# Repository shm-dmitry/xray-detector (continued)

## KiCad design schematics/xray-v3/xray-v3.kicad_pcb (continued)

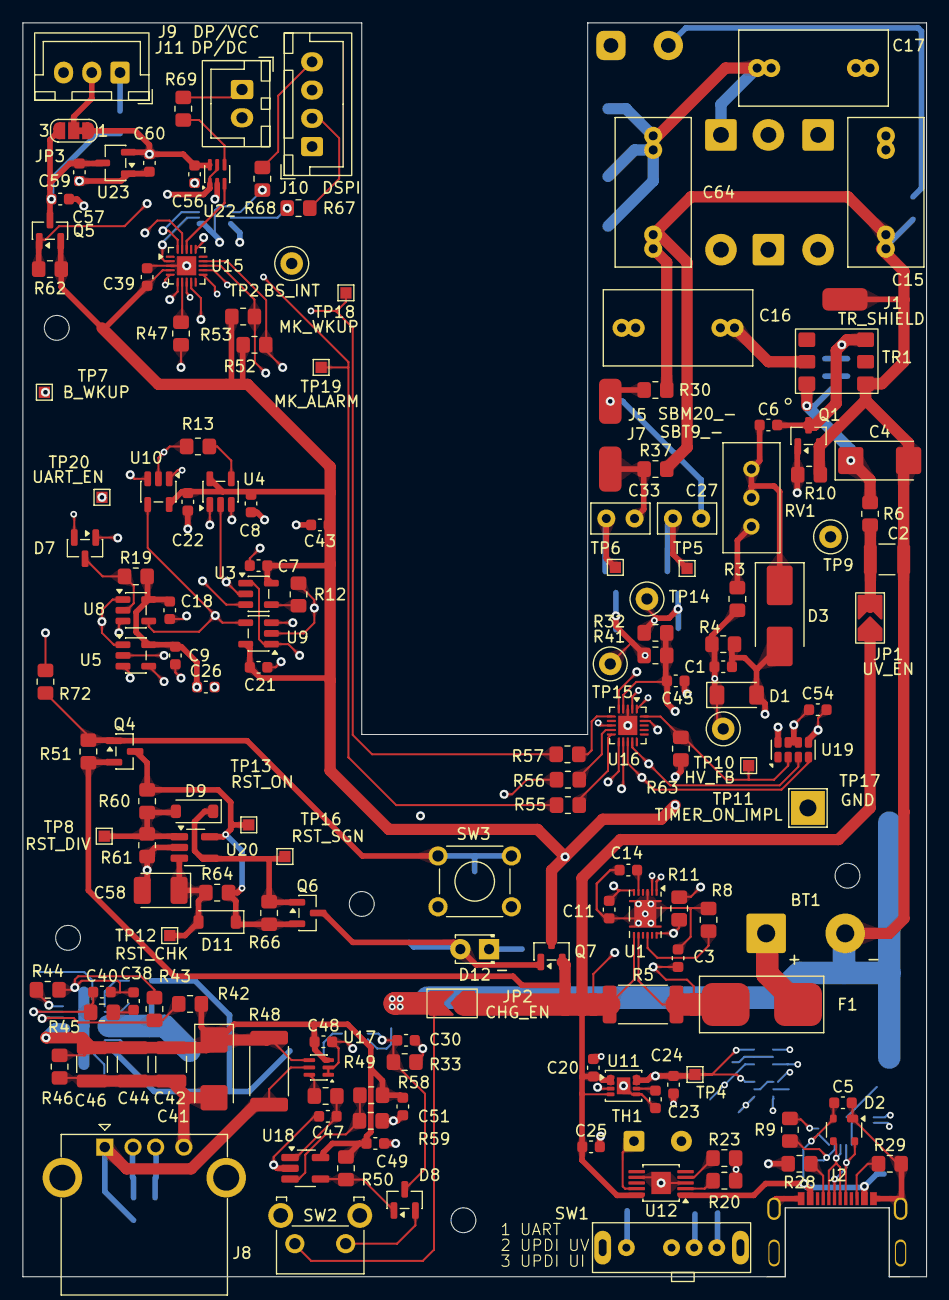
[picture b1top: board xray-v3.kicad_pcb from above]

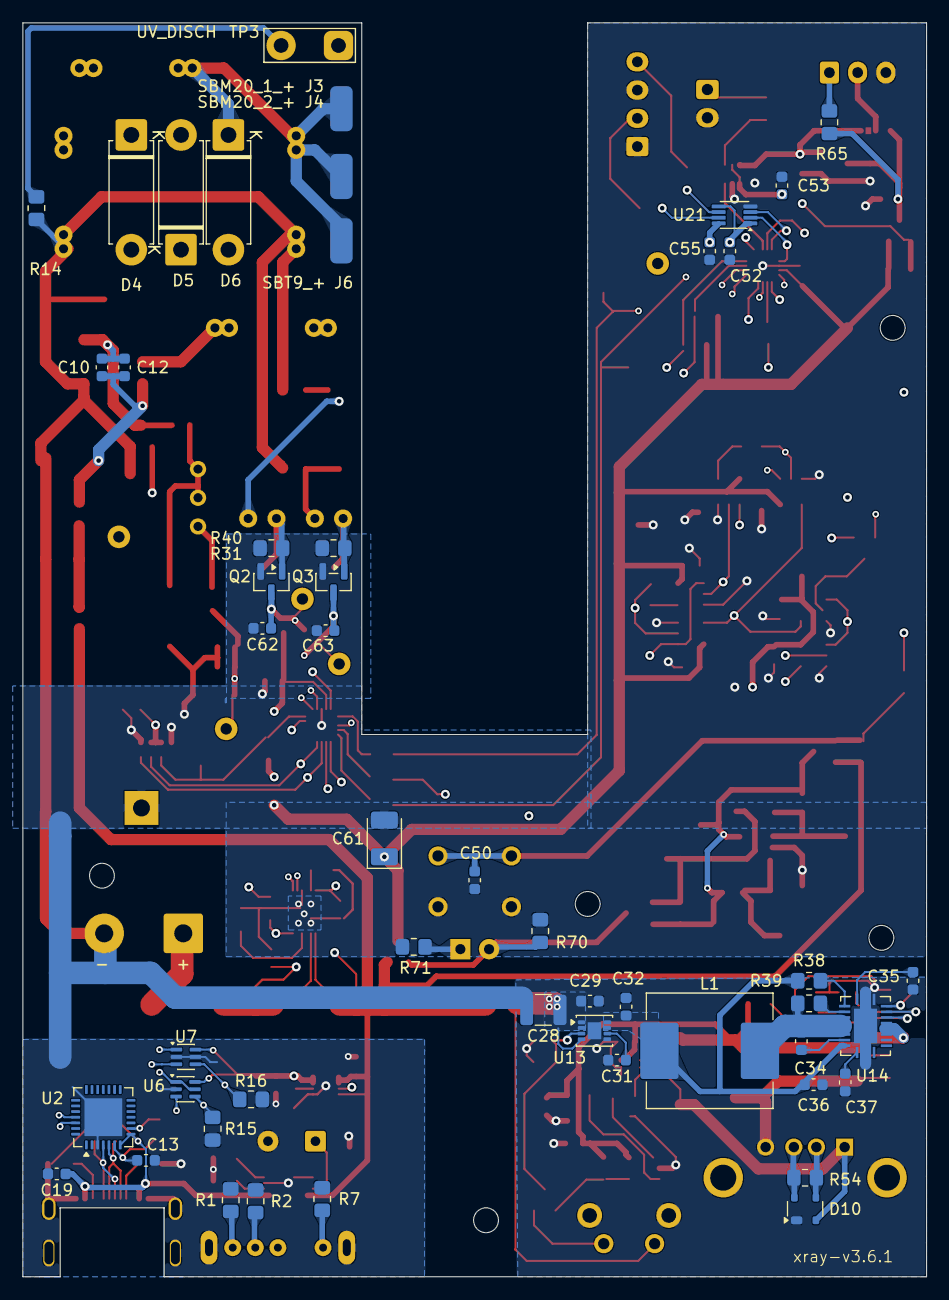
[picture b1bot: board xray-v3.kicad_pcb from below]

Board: 4 copper layers, 80.0 x 111.0 mm, 215 parts (51 on the bottom side), 109 nets.

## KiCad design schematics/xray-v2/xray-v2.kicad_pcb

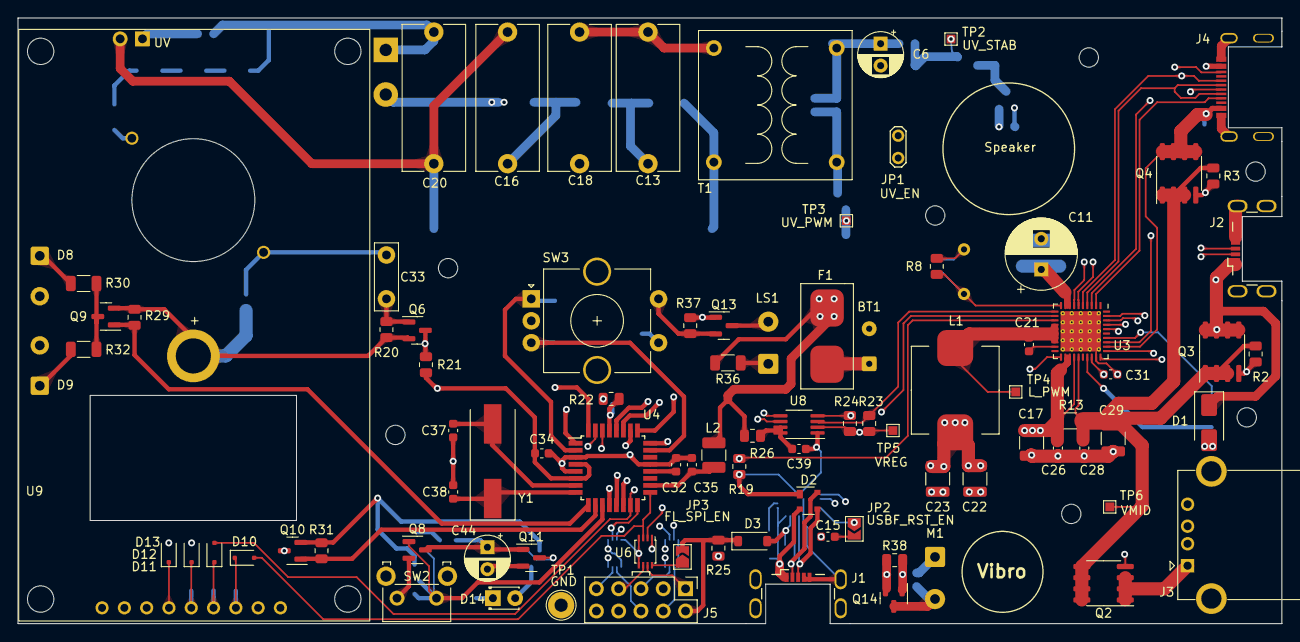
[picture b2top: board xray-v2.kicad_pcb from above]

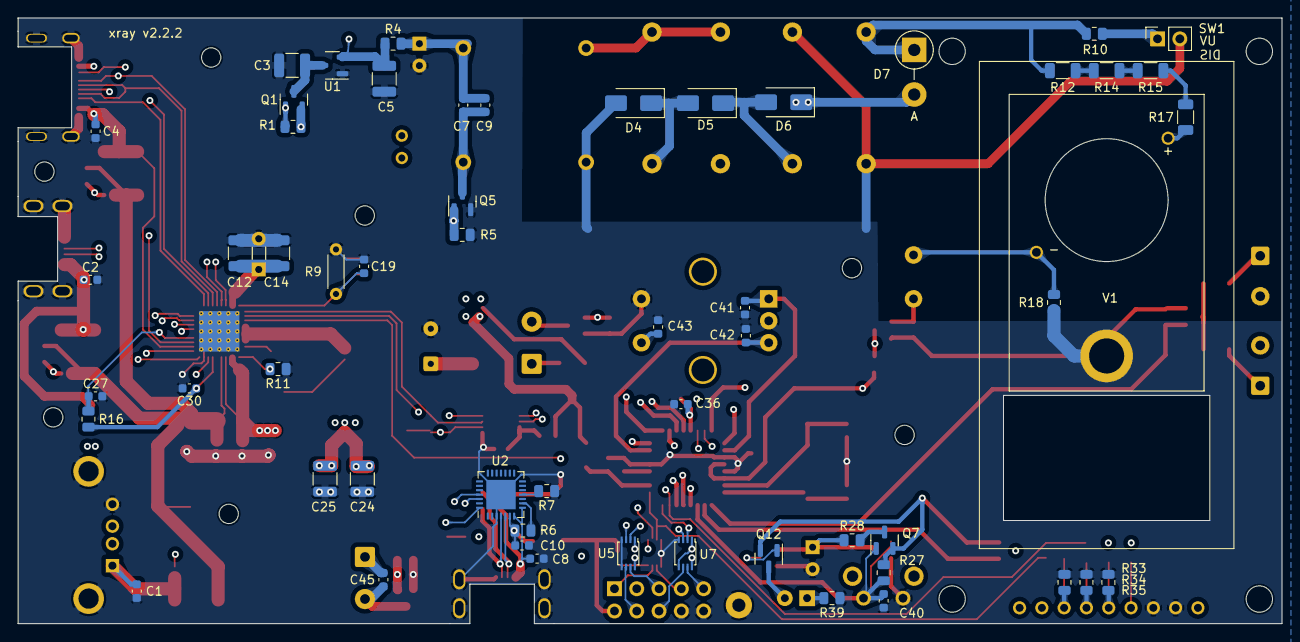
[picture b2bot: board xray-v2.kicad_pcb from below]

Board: 4 copper layers, 144.0 x 69.0 mm, 154 parts (56 on the bottom side), 101 nets.

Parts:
BT1: Li-Ion, 4.2V, 10000 mAh, 1260100; SolderWire-0.15sqmm_1x02_P4mm_D0.5mm_OD1.5mm
C1, C2, C4, C8, C10, C27: 10 uF; C_0603_1608Metric
C3, C5, C12, C14, C17, C22, C23, C24, C25, C29: 22 uF; C_1210_3225Metric
C6, C44: 100 uF; CP_Radial_D5.0mm_P2.50mm
C7: 21 nF *; C_0603_1608Metric
C9: see note [*]; C_0603_1608Metric
C11: 220 uF; CP_Radial_D8.0mm_P3.50mm
C13, C16, C18, C20: К73-17, 0.1 uF, 630V; C_Rect_L16.5mm_W7.0mm_P15.00mm_MKT
C15, C19, C21, C26, C28, C32, C34, C36, C41, C42, C43, C45: 100 nF; C_0603_1608Metric
C30, C31: 2.2 uF; C_0603_1608Metric
C33: CC81, 10 pF, 630V; C_Disc_D7.5mm_W2.5mm_P5.00mm
C35: 470 nF; C_0603_1608Metric
C37, C38: 18 pF; C_0603_1608Metric
C39: 200 pF; C_0603_1608Metric
C40: 2 uF; C_0603_1608Metric
D1: 15MQ030NPBF; D_SMA
D2: SP0503BAHT; SOT-143
D3: MBR0520; D_SOD-123
D4, D5, D6: US1M; D_SMA
D7: US1M; D_5W_P5.08mm_Vertical_AnodeUp
D8, D9: FLASH; SolderWire-0.5sqmm_1x02_P4.6mm_D0.9mm_OD2.1mm
D10, D11, D12, D13: BAV21WS; D_SOD-323F
D14: L-2060YD; LED_D1.8mm_W3.3mm_H2.4mm
F1: 1808, 6A; FuseHolder1808
H1, H2, H3, H4, H5, H6, H7: MountingHole; MountingHole_2.2mm_M2
J1, J2: USB_B_Micro; USB_Micro-B
J3: USB_A
J4: USB_C_Receptacle_USB2.0; USB_C_P16_MIDMOUNT_1.6
J5: USBASP; PinHeader_2x05_P2.54mm_Vertical
JP1: UV_EN; TestPoint_2Pads_Pitch2.54mm_Drill0.8mm
JP2: USBF_RST_EN; SolderJumper-2_P1.3mm_Open_TrianglePad1.0x1.5mm
JP3: FL_SPI_EN; SolderJumper-2_P1.3mm_Open_TrianglePad1.0x1.5mm
L1: 2.2 uH; Ferrocore-HPI1040
L2: 20 uH; L_1210_3225Metric
LS1: Speaker, D13mm; SolderWire-0.5sqmm_1x02_P4.8mm_D0.9mm_OD2.3mm
M1: VibroMotor, 3V, 8x2.7mm; SolderWire-0.5sqmm_1x02_P4.8mm_D0.9mm_OD2.3mm
Q1, Q7, Q10, Q12: IRLML5203; SOT-23
Q2: IRF7832PbF; SOIC-8_3.9x4.9mm_P1.27mm
Q3, Q4: IRF7425PbF; SOIC-8_3.9x4.9mm_P1.27mm
Q5, Q8, Q9, Q11, Q13, Q14: IRLML0030; SOT-23
Q6: BC847; SOT-23
R1, R2, R3, R7, R16, R21, R22, R25, R27: 10K; R_0805_2012Metric
R4: 68; R_0805_2012Metric
R5, R18, R20, R26, R29, R31, R37, R38: 200K; R_0805_2012Metric
R6: 1K; R_0805_2012Metric
R8: 82K; R_0805_2012Metric
R9: NTCM-100K@25-B4250; R_Axial_DIN0204_L3.6mm_D1.6mm_P5.08mm_Horizontal
R10: 510; R_0805_2012Metric
R11: 114K; R_0805_2012Metric
R12, R14, R15, R17: 2M, 200V; R_1206_3216Metric
R13: 0.01; R_1206_3216Metric
R19: 510K; R_0805_2012Metric
R23, R24: 3.3K; R_0805_2012Metric
R28: 400K ****; R_0805_2012Metric
R30, R32: 16; R_1206_3216Metric
R33, R34, R35: 5K; R_0805_2012Metric
R36: 27; R_1206_3216Metric
R39: 620; R_0805_2012Metric
SW1: SW_Push; PinSocket_1x02_P2.54mm_Vertical
SW2: B3F3150; SW_Tactile_SKHH_Angled
SW3: EC11W****; RotaryEncoder_Alps_EC11E-Switch_Vertical_H20mm_CircularMoun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
T1: Transformer_1P_1S; transformator-4-sh4x4
TP1: GND; TestPoint_Loop_D2.54mm_Drill1.5mm_Beaded
TP2: UV_STAB; TestPoint_Pad_1.0x1.0mm
TP3: UV_PWM; TestPoint_Pad_1.0x1.0mm
TP4: L_PWM; TestPoint_Pad_1.0x1.0mm
TP5: VREG; TestPoint_Pad_1.0x1.0mm
TP6: VMID; TestPoint_Pad_1.0x1.0mm
U1: XC6206P282MR; SOT-23-3
U2: CP2102N-Axx-xQFN28; QFN-28-1EP_5x5mm_P0.5mm_EP3.35x3.35mm
U3: IP5328P; QFN-40-1EP_6x6mm_P0.5mm_EP4.6x4.6mm_ThermalVias
U4: ATmega328P-A; TQFP-32_7x7mm_P0.8mm
U5, U6, U7: SN74LVC2T45DCUR; VSSOP-8_2.4x2.1mm_P0.5mm
U8: PCA9306; MSOP-8_3x3mm_P0.65mm
U9: Display_2.2inch_ili9341
V1: SBT11A; SBT11
Y1: HC-49SM, 8MHz; Crystal_SMD_HC49-SD

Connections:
+5V: D3.1 (K), J5.2, JP3.2 (B), R25.2, U5.8 (VCCB), U7.8 (VCCB)
/DISPLAY_VCC: D13.2 (A), Q10.3 (D), U9.1 (VCC), U9.8 (LED)
CP2102_VREG: C10.1, D3.2 (A), R6.2, U2.6 (VDD)
ENCODER_A: C41.1, SW3.A, U4.2 (PD4)
ENCODER_B: C42.1, SW3.B, U4.23 (PC0)
ENCODER_CLICK: C43.1, SW3.S1, U4.12 (PB0)
FLASHLIGHT: Q9.1 (G), R29.2, U4.9 (PD5)
FLUSH_D+: D2.3 (K), J1.3 (D+), U2.4 (D+)
FLUSH_D-: D2.4 (K), J1.2 (D-), U2.5 (D-)
FLUSH_VBUS: C8.1, D1.2 (A), D2.2 (K), J1.1 (VBUS), U2.7 (VREGIN), U2.8 (VBUS)
GND: BT1.2 (-), C1.2, C2.2, C3.2, C4.2, C5.2, C6.2, C8.2, C10.2, C11.2, C12.2, C14.2, C16.1, C17.2, C19.1, C20.1, C22.2, C23.2, C24.2, C25.2, C26.2, C27.2, C28.2, C29.2, C30.2, C31.2, C32.2, C34.2, C35.2, C36.2, C37.2, C38.2, C39.1, C40.1, C41.2, C42.2, C43.2, C44.2, D2.1 (A), D4.2 (A), J1.4 (ID), J1.5 (GND), J1.6 (Shield), J2.4 (ID), J2.5 (GND), J2.6 (Shield), J3.4 (GND), J3.5 (Shield), J4.A1 (GND), J4.A12 (GND), J4.B1 (GND), J4.B12 (GND), J4.S1 (SHIELD), J5.8, J5.10, Q5.2 (S), Q6.2 (E), Q8.2 (S), Q9.2 (S), Q11.2 (S), Q13.2 (S), Q14.2 (S), R5.1, R7.1, R8.2, R9.2, R11.1, R18.1, R19.2, R20.1, R29.1, R33.2, R34.2, R35.2, R37.1, R38.1, R39.1, SW1.2, SW2.2, SW3.C, SW3.S2, T1.3 (SA), TP1.1, U1.1 (GND), U2.3 (GND), U2.29 (GND), U3.29 (AGND), U3.41 (EP), U4.3 (GND), U4.5 (GND), U4.21 (GND), U5.4 (GND), U5.5 (DIR), U6.4 (GND), U6.5 (DIR), U7.4 (GND), U8.1 (GND), U9.2 (GND), U9.3 (CS), V1.3 (S)
MCU_I2C_SCL: U4.28 (PC5), U8.6 (SCL2)
MCU_I2C_SDA: U4.27 (PC4), U8.5 (SDA2)
MISO: U4.16 (PB4), U7.2 (A1)
MOSI: D11.2 (A), U4.15 (PB3), U6.2 (A1)
unnamed: BT1.1 (+), F1.2
unnamed: C13.1, D4.1 (K), D5.2 (A)
unnamed: C16.2, D5.1 (K), D6.2 (A)
unnamed: C18.2, D6.1 (K), D7.2 (A)
unnamed: C20.2, D7.1 (K), R10.2, R12.1
unnamed: D8.1 (K), R30.2
unnamed: D9.1 (K), R32.2
unnamed: D10.1 (K), R35.1, U9.7 (SCK)
unnamed: D11.1 (K), R34.1, U9.6 (MOSI)
unnamed: D12.1 (K), R33.1, U9.5 (DC)
unnamed: D13.1 (K), U9.4 (RESET#)
unnamed: D14.2 (A), Q12.3 (D)
unnamed: D14.1 (K), R39.2
unnamed: J5.1, U6.7 (B1)
unnamed: J5.7, U6.6 (B2)
unnamed: J5.9, U7.7 (B1)
unnamed: JP1.2 (B), Q1.1 (G), R1.1
unnamed: JP2.1 (A), U2.28 (~DTR)
unnamed: C15.1, JP2.2 (B)
unnamed: JP3.1 (A), U6.8 (VCCB)
unnamed: LS1.1, R36.1
unnamed: C45.1, M1.2 (-), Q14.3 (D)
unnamed: C3.1, Q1.3 (D), U1.3 (VI)
unnamed: C7.1, C9.1, Q5.3 (D), T1.2 (AB)
unnamed: C33.2, Q6.1 (B), R20.2
unnamed: Q7.3 (D), R28.2
unnamed: Q9.3 (D), R30.1, R32.1
unnamed: C44.1, Q8.3 (D), Q11.1 (G), R28.1
unnamed: LS1.2, Q13.3 (D)
unnamed: R10.1, SW1.1
unnamed: R12.2, R14.1
unnamed: R14.2, R15.1
unnamed: R15.2, R17.1
unnamed: C6.1, C7.2, C9.2, R4.2, T1.1 (AA)
unnamed: C13.2, C18.1, T1.4 (SB)
unnamed: C5.1, R4.1, TP2.1, U1.2 (VO)
unnamed: R6.1, U2.9 (~RST)
unnamed: R7.2, U2.11 (~SUSPEND)
unnamed: C21.1, U3.19 (BST)
unnamed: C21.2, L1.2, TP4.1, U3.14 (LX_1), U3.15 (LX_2), U3.16 (LX_3), U3.17 (LX_4), U3.18 (LX_5)
unnamed: C19.2, R8.1, R9.1, U3.10 (NTC)
unnamed: R11.2, U3.21 (RSET)
unnamed: C32.1, U4.20 (AREF)
unnamed: C35.1, L2.1, U4.18 (AVCC)
unnamed: C37.1, U4.7 (XTAL1/PB6), Y1.2
unnamed: C38.1, U4.8 (XTAL2/PB7), Y1.1
unnamed: C39.2, R26.2, U8.7 (VREF2), U8.8 (EN)
unnamed: R17.2, V1.1 (A)
unnamed: C33.1, R18.2, V1.2 (C)
RADIATION_VALUE: Q6.3 (C), R21.1, U4.32 (PD2)
RESET: C36.1, Q11.3 (D), Q12.1 (G), R22.1, U4.29 (~RESET/PC6), U5.2 (A1)
RESET_V: C15.2, J5.5, R25.1, U5.7 (B1)
RXD: U4.30 (PD0), U5.3 (A2)
RXD_V: J5.4, U2.26 (TXD), U5.6 (B2)
SCK: D10.2 (A), U4.17 (PB5), U6.3 (A2)
SPEAKER: Q13.1 (G), R37.2, U4.1 (PD3)
TFT_DC: D12.2 (A), U4.26 (PC3)
TFT_ENABLE#: Q10.1 (G), R31.1, U4.10 (PD6)
TXD: U4.31 (PD1), U7.3 (A2)
TXD_V: J5.6, U2.25 (RXD), U7.6 (B2)
USB_I2C_SCL: R23.2, U3.11 (L1), U8.3 (SCL1)
USB_I2C_SDA: R24.2, U3.12 (L2), U8.4 (SDA1)
USB_INT: R19.1, U3.13 (L3), U4.13 (PB1)
USB_IN_CC1: J4.A5 (CC1), U3.2 (CC1)
USB_IN_CC2: J4.B5 (CC2), U3.3 (CC2)
USB_IN_D+: J4.A6 (D+), J4.B6 (D+), U3.5 (DPC)
USB_IN_D-: J4.A7 (D-), J4.B7 (D-), U3.4 (DMC)
USB_IN_VBUS: C4.1, J4.A4 (VBUS), J4.A9 (VBUS), J4.B4 (VBUS), J4.B9 (VBUS), Q4.5 (D), Q4.6 (D), Q4.7 (D), Q4.8 (D), U3.32 (VBUS)
USB_IN_VBUS_G: Q4.4 (G), R3.1, U3.33 (VBUSG)
USB_M_IN_D+: J2.3 (D+), U3.7 (DPB)
USB_M_IN_D-: J2.2 (D-), U3.6 (DMB)
USB_M_IN_VBUS: C2.1, D1.1 (K), J2.1 (VBUS), Q3.5 (D), Q3.6 (D), Q3.7 (D), Q3.8 (D), U3.30 (VIN)
USB_M_IN_VBUS_G: Q3.4 (G), R2.1, U3.31 (VING)
USB_OUT_D+: J3.3 (D+), U3.39 (DPA1)
USB_OUT_D-: J3.2 (D-), U3.38 (DMA1)
USB_OUT_VBUS: C1.1, J3.1 (VBUS), Q2.1 (S), Q2.2 (S), Q2.3 (S), U3.37 (VOUT1)
USB_OUT_VBUS_G: Q2.4 (G), U3.36 (VOUT1G)
USB_OUT_VOUT2: C27.1, R16.2, U3.34 (VOUT2)
USB_VMID: C28.1, C29.1, Q2.5 (D), Q2.6 (D), Q2.7 (D), Q2.8 (D), Q3.1 (S), Q3.2 (S), Q3.3 (S), Q4.1 (S), Q4.2 (S), Q4.3 (S), R2.2, R3.2, R13.1, TP6.1, U3.25 (VSN)
USB_VSYS: C11.1, C12.1, C14.1, C17.1, C26.1, R13.2, U3.8 (VSYS_1), U3.9 (VSYS_2), U3.22 (VSYS_3), U3.23 (VSYS_4), U3.24 (VSP)
UV_ENABLE#: JP1.1 (A), U4.25 (PC2)
UV_PWM: Q5.1 (G), R5.2, TP3.1, U4.14 (PB2)
VCC: C22.1, C23.1, C24.1, C25.1, C31.1, C34.1, C45.2, D8.2 (A), D9.2 (A), F1.1, L1.1, L2.2, M1.1 (+), Q1.2 (S), Q7.2 (S), Q10.2 (S), Q12.2 (S), R1.2, R21.2, R22.2, R26.1, R27.2, R31.2, R36.2, U3.28 (BAT), U4.4 (VCC), U4.6 (VCC), U5.1 (VCCA), U6.1 (VCCA), U7.1 (VCCA), U7.5 (DIR)
VIBRO: Q14.1 (G), R38.2, U4.24 (PC1)
VREG: C30.1, R16.1, R23.1, R24.1, TP5.1, U3.27 (VREG), U8.2 (VREF1)
WAKEUP_BUTTON: C40.2, Q7.1 (G), Q8.1 (G), R27.1, SW2.1, U4.11 (PD7)

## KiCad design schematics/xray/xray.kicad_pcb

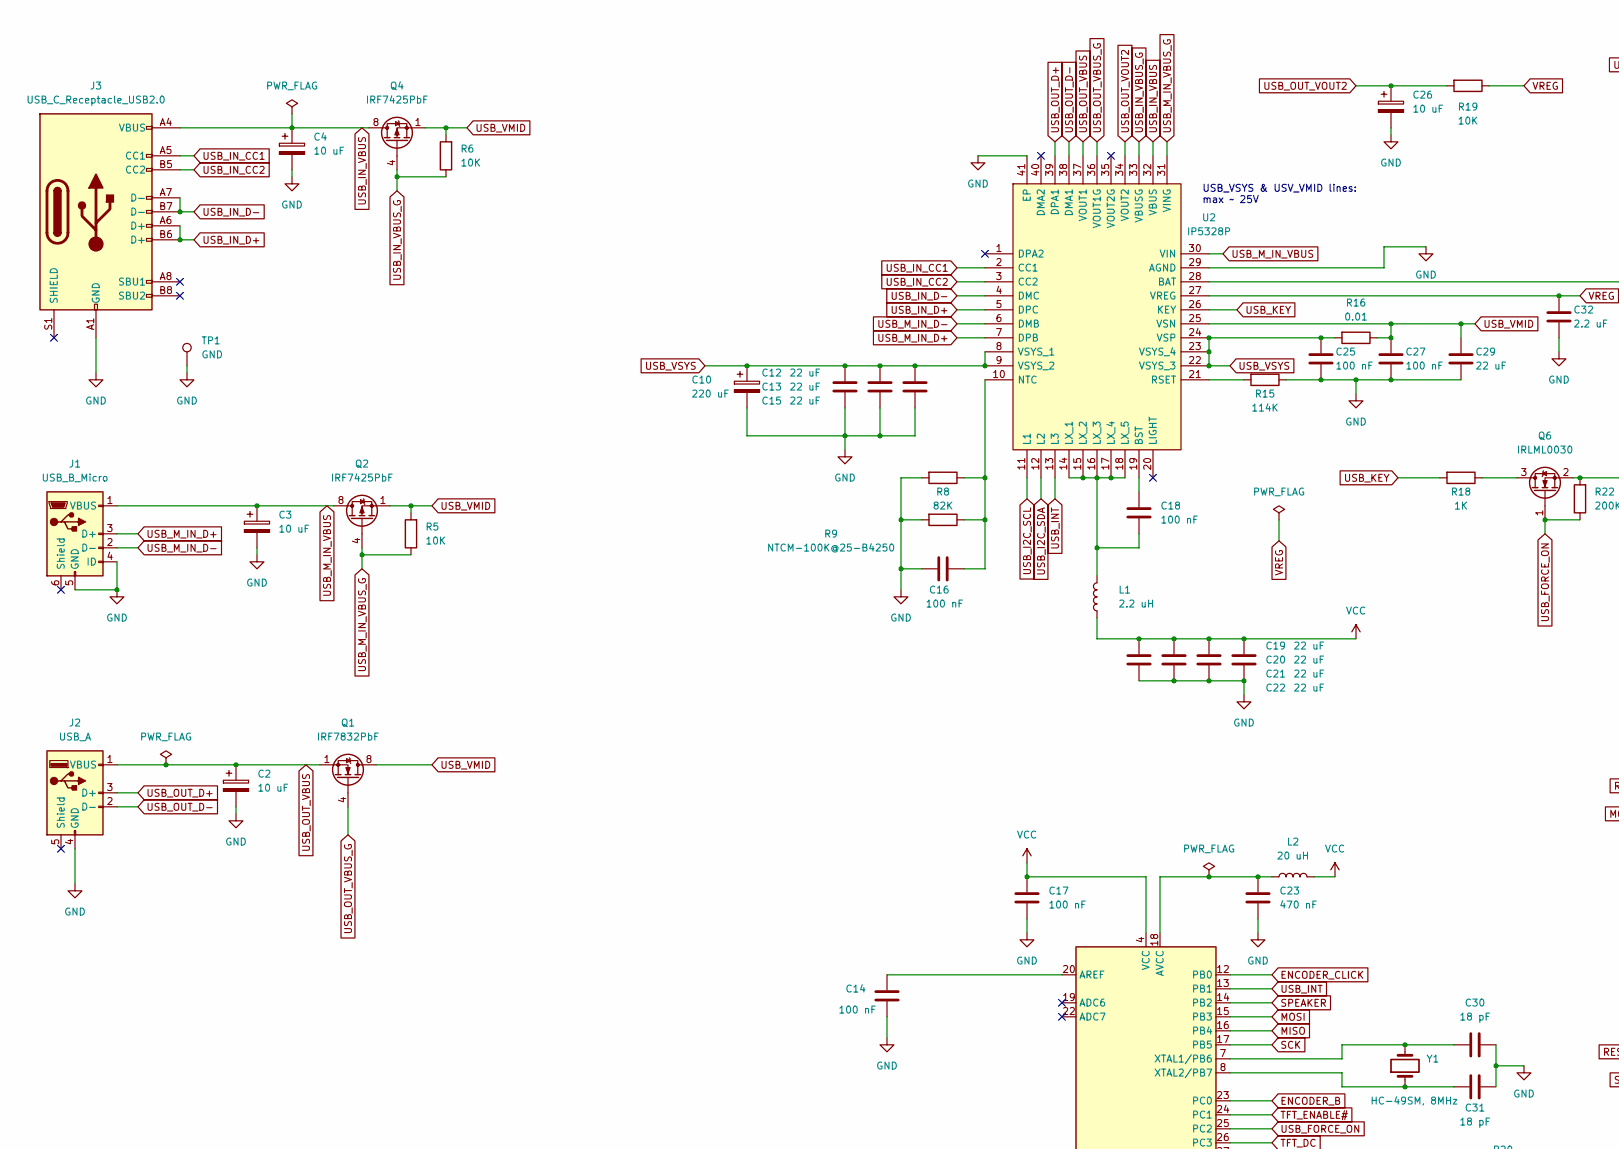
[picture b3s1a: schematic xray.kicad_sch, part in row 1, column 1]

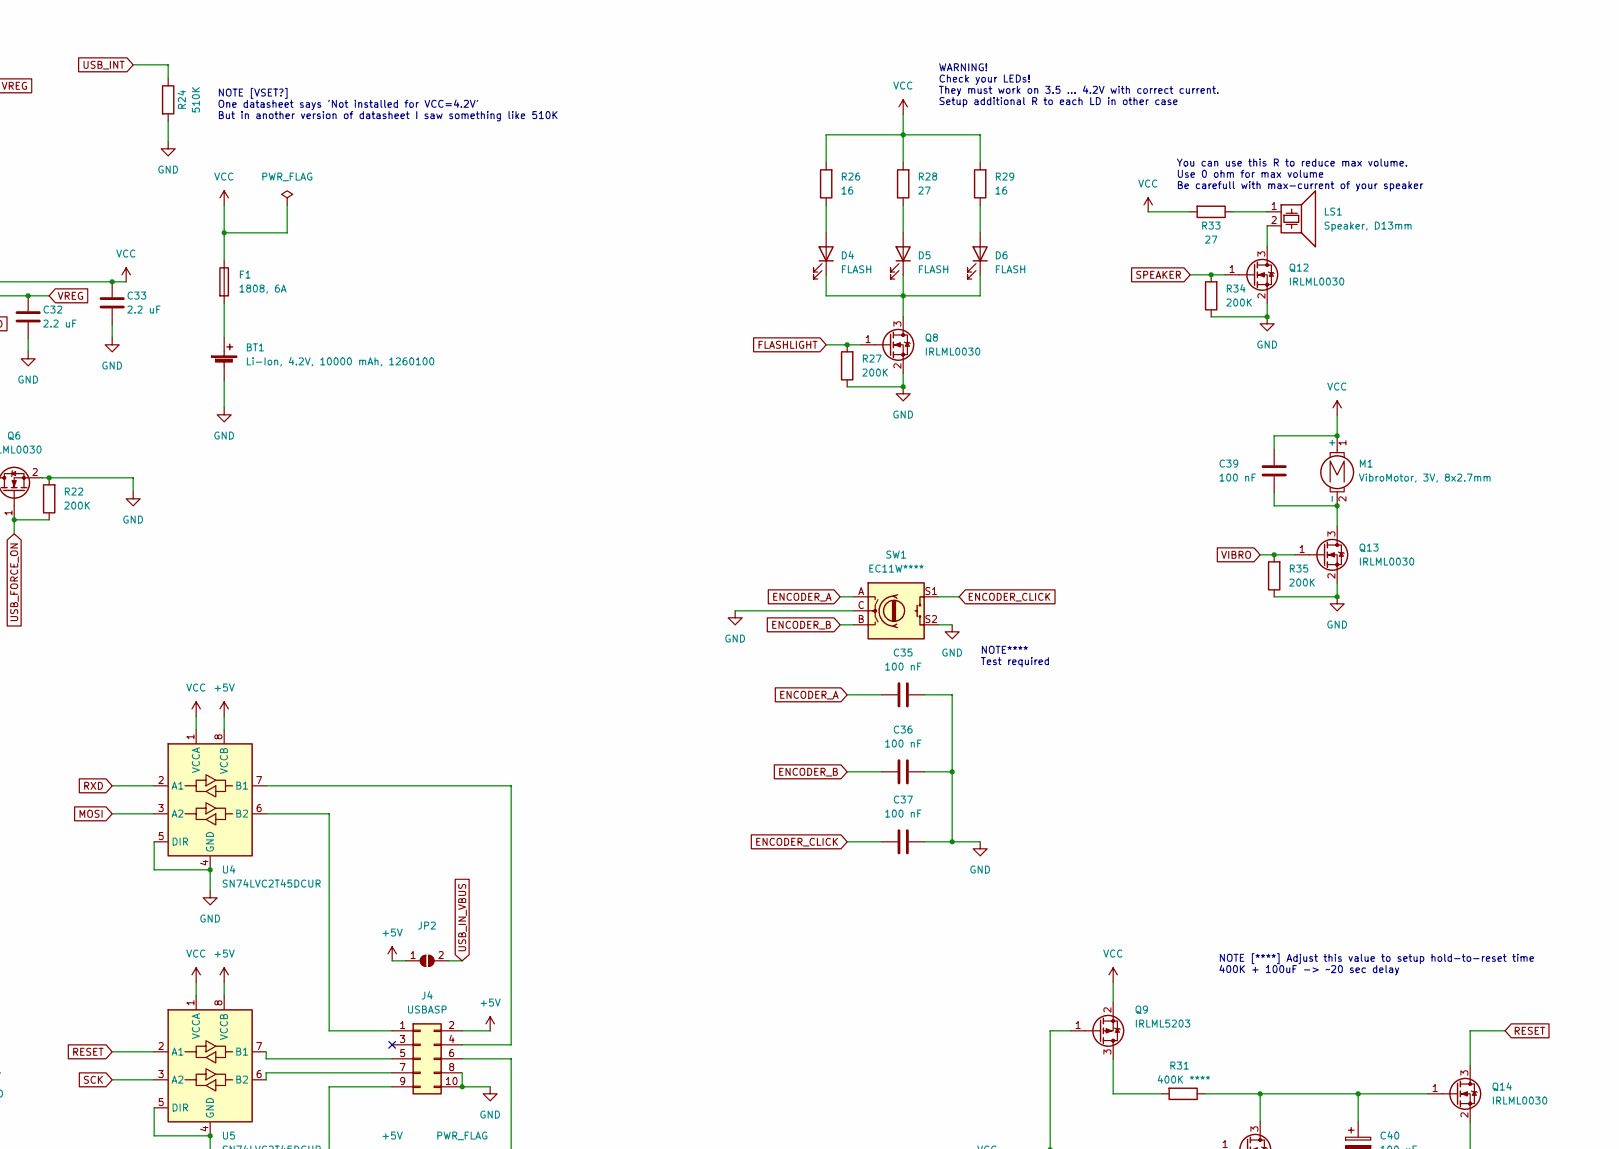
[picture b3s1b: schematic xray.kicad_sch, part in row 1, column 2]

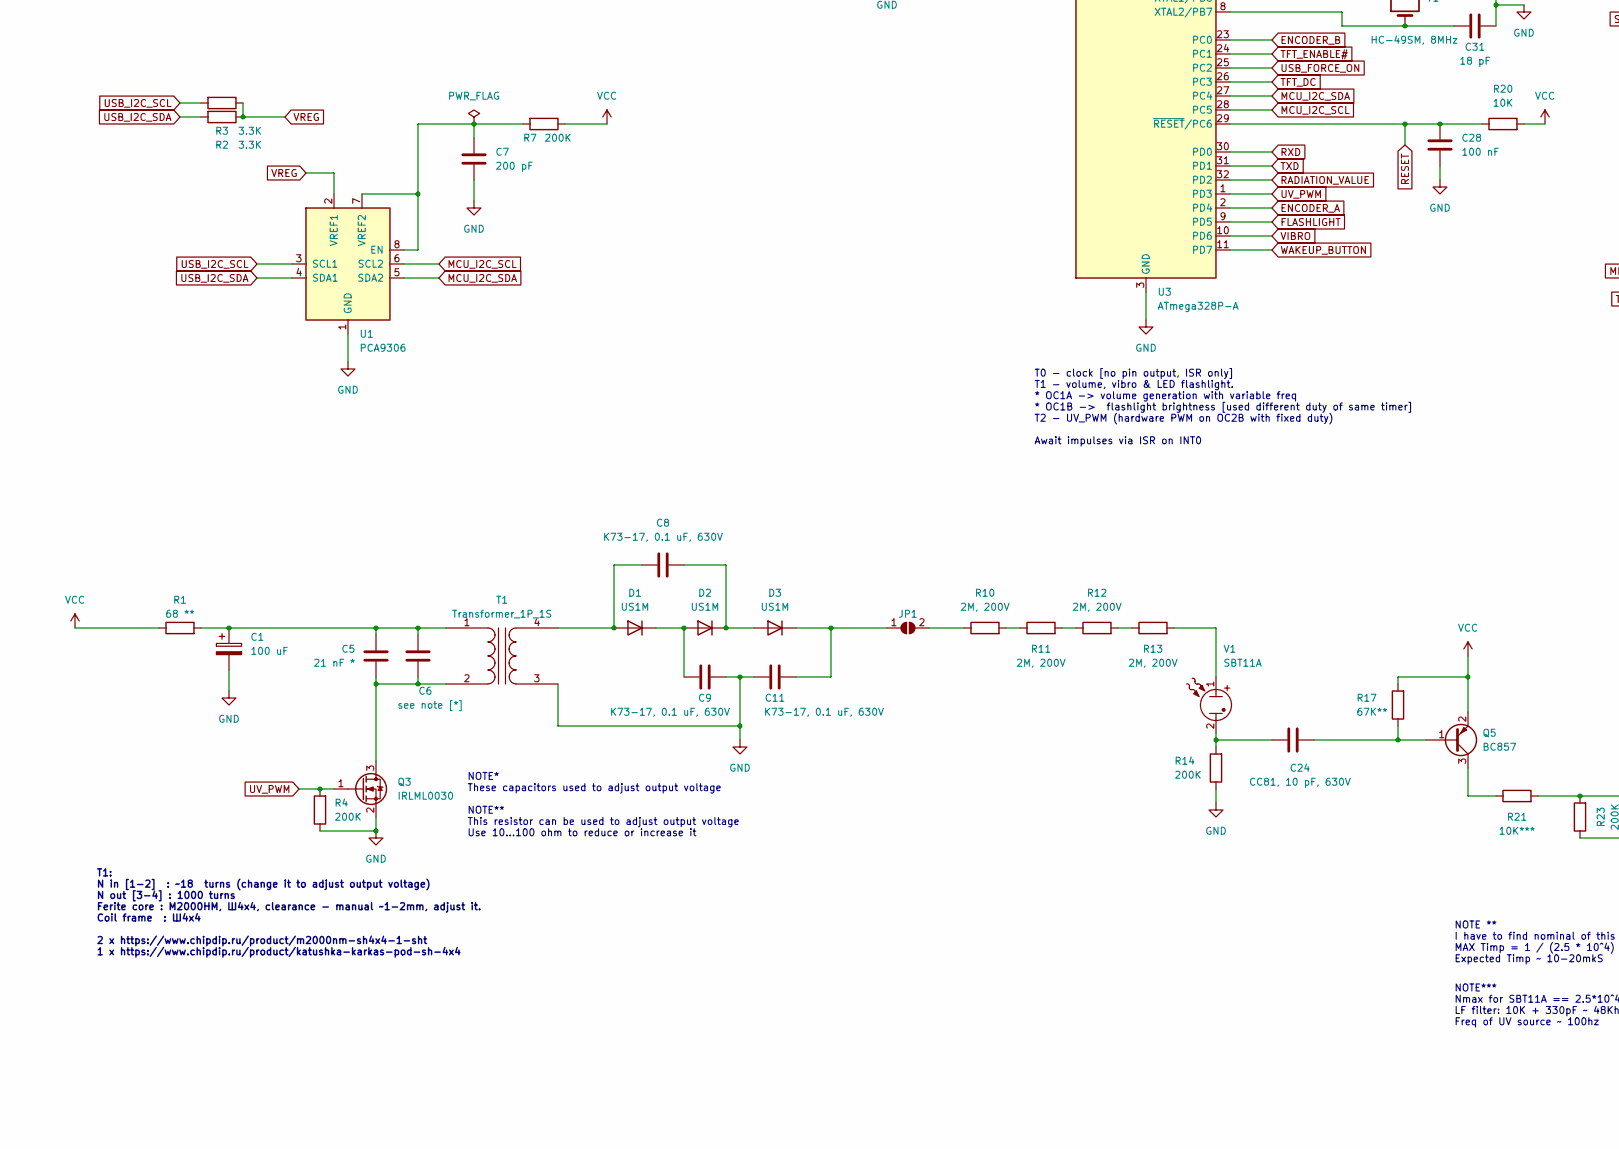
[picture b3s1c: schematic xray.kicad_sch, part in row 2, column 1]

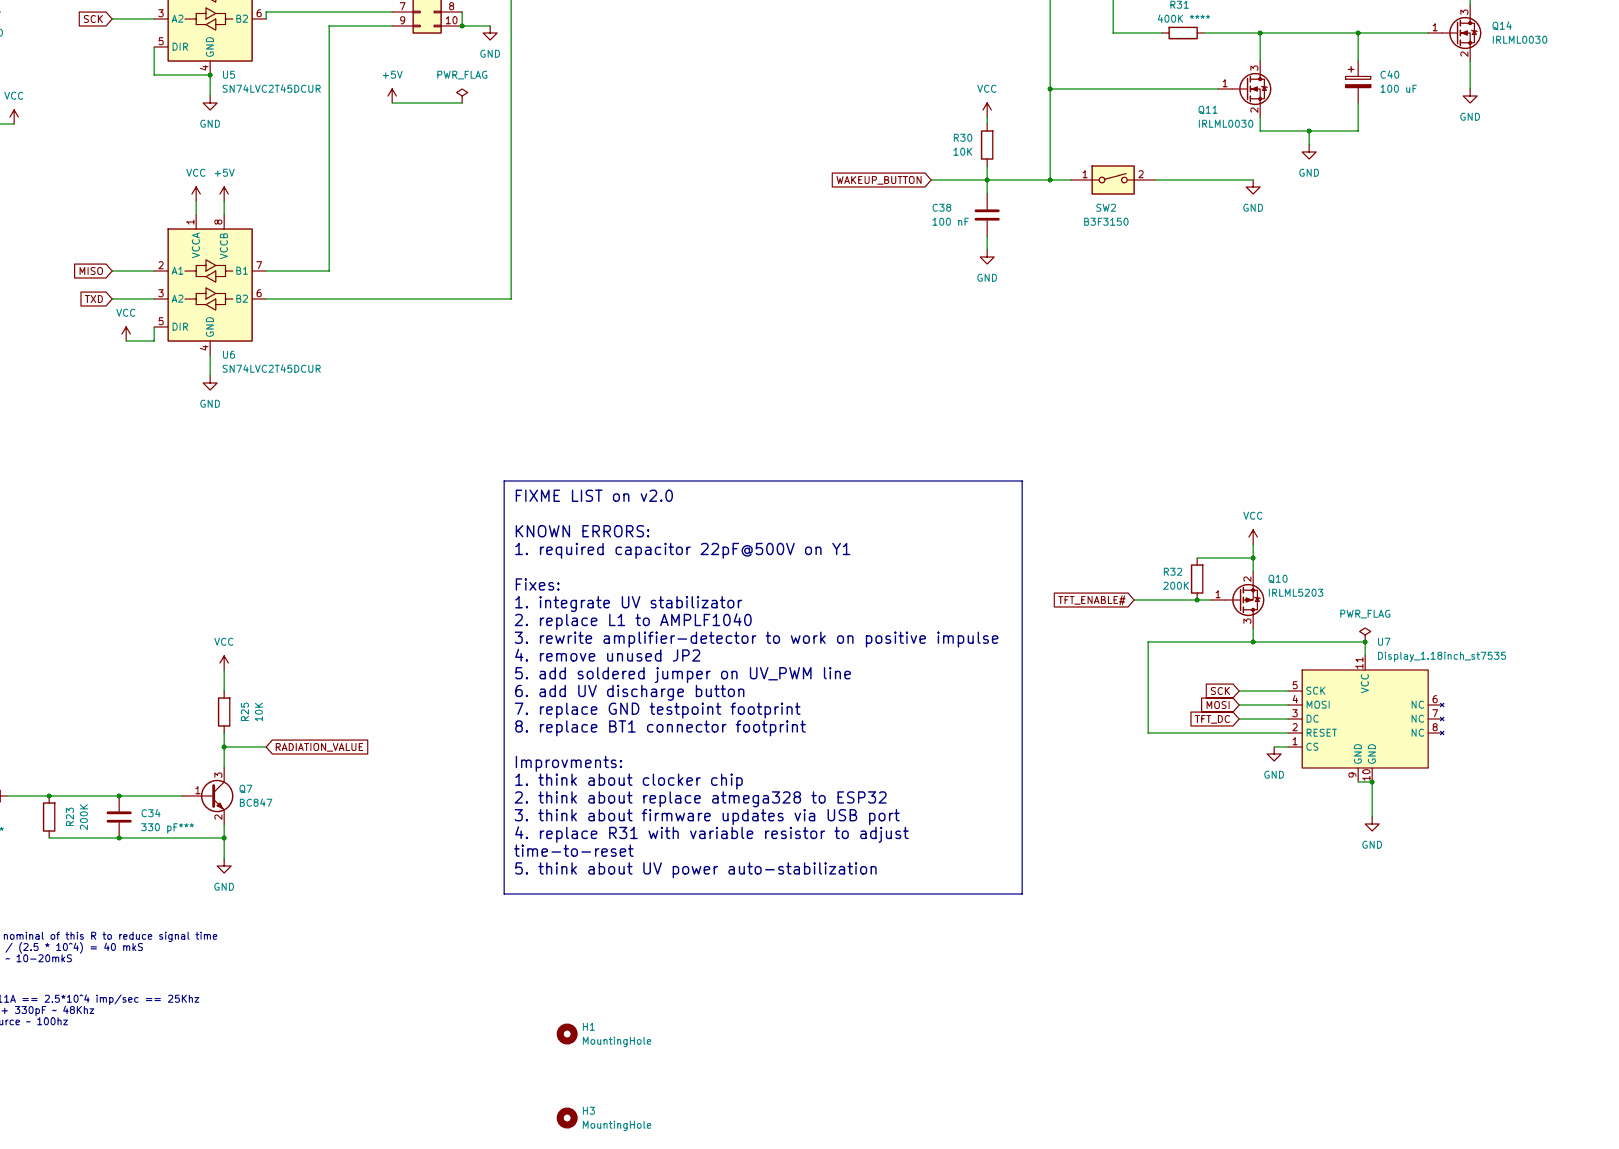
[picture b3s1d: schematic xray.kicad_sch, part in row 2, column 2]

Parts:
BT1: Li-Ion, 4.2V, 10000 mAh, 1260100; SolderWire-0.15sqmm_1x02_P4mm_D0.5mm_OD1.5mm
C1, C40: 100 uF; CP_Radial_D5.0mm_P2.50mm
C2, C3, C4, C26: 10 uF; CP_Radial_D5.0mm_P2.00mm
C5: 21 nF *; C_0603_1608Metric
C6: see note [*]; C_0603_1608Metric
C7: 200 pF; C_0603_1608Metric
C8, C9, C11: К73-17, 0.1 uF, 630V; C_Rect_L16.5mm_W9.0mm_P15.00mm_MKT
C10: 220 uF; CP_Radial_D8.0mm_P3.50mm
C12, C13, C15, C19, C20, C21, C22, C29: 22 uF; C_1210_3225Metric
C14, C16, C17, C18, C25, C27, C28, C35, C36, C37, C38, C39: 100 nF; C_0603_1608Metric
C23: 470 nF; C_0603_1608Metric
C24: CC81, 10 pF, 630V; C_Disc_D7.5mm_W2.5mm_P5.00mm
C30, C31: 18 pF; C_0603_1608Metric
C32, C33: 2.2 uF; C_0603_1608Metric
C34: 330 pF***; C_0603_1608Metric
D1, D2: US1M; D_SMA
D3: US1M; D_5W_P5.08mm_Vertical_AnodeUp
D4, D5, D6: FLASH; SolderWire-0.5sqmm_1x02_P4.6mm_D0.9mm_OD2.1mm
F1: 1808, 6A; FuseHolder1808
H1, H3: MountingHole; MountingHole_3.2mm_M3
J1: USB_B_Micro; USB_Micro-B
J2: USB_A
J3: USB_C_Receptacle_USB2.0; USB_C_P16_MIDMOUNT_1.6
J4: USBASP; PinHeader_2x05_P2.54mm_Vertical
JP1, JP2: SolderJumper_2_Open; SolderJumper-2_P1.3mm_Open_TrianglePad1.0x1.5mm
L1: 2.2 uH; L_Sumida_CDMC6D28_7.25x6.5mm
L2: 20 uH; L_1210_3225Metric
LS1: Speaker, D13mm; SolderWire-0.5sqmm_1x02_P4.8mm_D0.9mm_OD2.3mm
M1: VibroMotor, 3V, 8x2.7mm; SolderWire-0.5sqmm_1x02_P4.8mm_D0.9mm_OD2.3mm
Q1: IRF7832PbF; SOIC-8_3.9x4.9mm_P1.27mm
Q2, Q4: IRF7425PbF; SOIC-8_3.9x4.9mm_P1.27mm
Q3, Q6, Q8, Q11, Q12, Q13, Q14: IRLML0030; SOT-23
Q5: BC857; SOT-23
Q7: BC847; SOT-23
Q9, Q10: IRLML5203; SOT-23
R1: 68 **; R_0805_2012Metric
R2, R3: 3.3K; R_0805_2012Metric
R4, R7, R14, R22, R23, R27, R32, R34, R35: 200K; R_0805_2012Metric
R5, R6, R19, R20, R25, R30: 10K; R_0805_2012Metric
R8: 82K; R_0805_2012Metric
R9: NTCM-100K@25-B4250; R_Axial_DIN0204_L3.6mm_D1.6mm_P5.08mm_Horizontal
R10, R11, R12, R13: 2M, 200V; R_1206_3216Metric
R15: 114K; R_0805_2012Metric
R16: 0.01; R_1206_3216Metric
R17: 67K**; R_0805_2012Metric
R18: 1K; R_0805_2012Metric
R21: 10K***; R_0805_2012Metric
R24: 510K; R_0805_2012Metric
R26, R29: 16; R_1206_3216Metric
R28, R33: 27; R_1206_3216Metric
R31: 400K ****; R_0805_2012Metric
SW1: EC11W****; RotaryEncoder_Alps_EC11E-Switch_Vertical_H20mm_CircularMoun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
SW2: B3F3150; SW_Tactile_SKHH_Angled
T1: Transformer_1P_1S; transformator-4-sh4x4
TP1: GND; TestPoint_Pad_4.0x4.0mm
U1: PCA9306; MSOP-8_3x3mm_P0.65mm
U2: IP5328P; QFN-40-1EP_6x6mm_P0.5mm_EP4.6x4.6mm_ThermalVias; Manufacturer_Part_Number IP5328P
U3: ATmega328P-A; TQFP-32_7x7mm_P0.8mm
U4, U5, U6: SN74LVC2T45DCUR; VSSOP-8_2.4x2.1mm_P0.5mm
U7: Display_1.18inch_st7535; Display_1.18inch_st7735
V1: SBT11A; SBT11
Y1: HC-49SM, 8MHz; Crystal_SMD_HC49-SD

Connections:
+5V: J4.2, JP2.1 (A), U4.8 (VCCB), U5.8 (VCCB), U6.8 (VCCB)
ENCODER_A: C35.1, SW1.A, U3.2 (PD4)
ENCODER_B: C36.1, SW1.B, U3.23 (PC0)
ENCODER_CLICK: C37.1, SW1.S1, U3.12 (PB0)
FLASHLIGHT: Q8.1 (G), R27.2, U3.9 (PD5)
GND: BT1.2 (-), C1.2, C2.2, C3.2, C4.2, C7.1, C9.2, C10.2, C11.1, C12.2, C13.2, C14.2, C15.2, C16.1, C17.2, C19.2, C20.2, C21.2, C22.2, C23.2, C25.2, C26.2, C27.2, C28.2, C29.2, C30.2, C31.2, C32.2, C33.2, C34.1, C35.2, C36.2, C37.2, C38.1, C40.2, J1.4 (ID), J1.5 (GND), J2.4 (GND), J3.A1 (GND), J3.A12 (GND), J3.B1 (GND), J3.B12 (GND), J4.8, J4.10, Q3.2 (S), Q6.2 (S), Q7.2 (E), Q8.2 (S), Q11.2 (S), Q12.2 (S), Q13.2 (S), Q14.2 (S), R4.1, R8.2, R9.2, R14.1, R15.1, R22.2, R23.1, R24.2, R27.1, R34.1, R35.1, SW1.C, SW1.S2, SW2.2, T1.3 (SA), TP1.1, U1.1 (GND), U2.29 (AGND), U2.41 (EP), U3.3 (GND), U3.5 (GND), U3.21 (GND), U4.4 (GND), U4.5 (DIR), U5.4 (GND), U5.5 (DIR), U6.4 (GND), U7.1 (CS), U7.9 (GND), U7.10 (GND)
MCU_I2C_SCL: U1.6 (SCL2), U3.28 (PC5)
MCU_I2C_SDA: U1.5 (SDA2), U3.27 (PC4)
MISO: U3.16 (PB4), U6.2 (A1)
MOSI: U3.15 (PB3), U4.3 (A2), U7.4 (MOSI)
unnamed: BT1.1 (+), F1.2
unnamed: C24.1, R14.2, V1.2
unnamed: C8.1, D1.2 (A), T1.4 (SB)
unnamed: C9.1, D1.1 (K), D2.2 (A)
unnamed: C8.2, D2.1 (K), D3.2 (A)
unnamed: C11.2, D3.1 (K), JP1.1 (A)
unnamed: D4.2 (A), R26.1
unnamed: D4.1 (K), D5.1 (K), D6.1 (K), Q8.3 (D)
unnamed: D5.2 (A), R28.1
unnamed: D6.2 (A), R29.1
unnamed: J4.1, U4.6 (B2)
unnamed: J4.4, U4.7 (B1)
unnamed: J4.5, U5.7 (B1)
unnamed: J4.6, U6.6 (B2)
unnamed: J4.7, U5.6 (B2)
unnamed: J4.9, U6.7 (B1)
unnamed: JP1.2 (B), R10.1
unnamed: LS1.1, R33.1
unnamed: C39.1, M1.2 (-), Q13.3 (D)
unnamed: C5.1, C6.1, Q3.3 (D), T1.2 (AB)
unnamed: C24.2, Q5.1 (B), R17.1
unnamed: Q5.3 (C), R21.1
unnamed: Q6.3 (D), R18.1
unnamed: C34.2, Q7.1 (B), R21.2, R23.2
unnamed: Q9.3 (D), R31.2
unnamed: Q10.3 (D), U7.2 (RESET), U7.11 (VCC)
unnamed: C40.1, Q11.3 (D), Q14.1 (G), R31.1
unnamed: LS1.2, Q12.3 (D)
unnamed: R10.2, R11.1
unnamed: R11.2, R12.1
unnamed: R12.2, R13.1
unnamed: R13.2, V1.1
unnamed: C1.1, C5.2, C6.2, R1.2, T1.1 (AA)
unnamed: C7.2, R7.2, U1.7 (VREF2), U1.8 (EN)
unnamed: C18.1, U2.19 (BST)
unnamed: C18.2, L1.2, U2.14 (LX_1), U2.15 (LX_2), U2.16 (LX_3), U2.17 (LX_4), U2.18 (LX_5)
unnamed: C16.2, R8.1, R9.1, U2.10 (NTC)
unnamed: R15.2, U2.21 (RSET)
unnamed: C14.1, U3.20 (AREF)
unnamed: C23.1, L2.1, U3.18 (AVCC)
unnamed: C30.1, U3.7 (XTAL1/PB6), Y1.2
unnamed: C31.1, U3.8 (XTAL2/PB7), Y1.1
RADIATION_VALUE: Q7.3 (C), R25.1, U3.32 (PD2)
RESET: C28.1, Q14.3 (D), R20.1, U3.29 (~RESET/PC6), U5.2 (A1)
RXD: U3.30 (PD0), U4.2 (A1)
SCK: U3.17 (PB5), U5.3 (A2), U7.5 (SCK)
SPEAKER: Q12.1 (G), R34.2, U3.14 (PB2)
TFT_DC: U3.26 (PC3), U7.3 (DC)
TFT_ENABLE#: Q10.1 (G), R32.1, U3.24 (PC1)
TXD: U3.31 (PD1), U6.3 (A2)
USB_FORCE_ON: Q6.1 (G), R22.1, U3.25 (PC2)
USB_I2C_SCL: R2.2, U1.3 (SCL1), U2.11 (L1)
USB_I2C_SDA: R3.2, U1.4 (SDA1), U2.12 (L2)
USB_INT: R24.1, U2.13 (L3), U3.13 (PB1)
USB_IN_CC1: J3.A5 (CC1), U2.2 (CC1)
USB_IN_CC2: J3.B5 (CC2), U2.3 (CC2)
USB_IN_D+: J3.A6 (D+), J3.B6 (D+), U2.5 (DPC)
USB_IN_D-: J3.A7 (D-), J3.B7 (D-), U2.4 (DMC)
USB_IN_VBUS: C4.1, J3.A4 (VBUS), J3.A9 (VBUS), J3.B4 (VBUS), J3.B9 (VBUS), JP2.2 (B), Q4.5 (D), Q4.6 (D), Q4.7 (D), Q4.8 (D), U2.32 (VBUS)
USB_IN_VBUS_G: Q4.4 (G), R6.1, U2.33 (VBUSG)
USB_KEY: R18.2, U2.26 (KEY)
USB_M_IN_D+: J1.3 (D+), U2.7 (DPB)
USB_M_IN_D-: J1.2 (D-), U2.6 (DMB)
USB_M_IN_VBUS: C3.1, J1.1 (VBUS), Q2.5 (D), Q2.6 (D), Q2.7 (D), Q2.8 (D), U2.30 (VIN)
USB_M_IN_VBUS_G: Q2.4 (G), R5.1, U2.31 (VING)
USB_OUT_D+: J2.3 (D+), U2.39 (DPA1)
USB_OUT_D-: J2.2 (D-), U2.38 (DMA1)
USB_OUT_VBUS: C2.1, J2.1 (VBUS), Q1.1 (S), Q1.2 (S), Q1.3 (S), U2.37 (VOUT1)
USB_OUT_VBUS_G: Q1.4 (G), U2.36 (VOUT1G)
USB_OUT_VOUT2: C26.1, R19.2, U2.34 (VOUT2)
USB_VMID: C27.1, C29.1, Q1.5 (D), Q1.6 (D), Q1.7 (D), Q1.8 (D), Q2.1 (S), Q2.2 (S), Q2.3 (S), Q4.1 (S), Q4.2 (S), Q4.3 (S), R5.2, R6.2, R16.1, U2.25 (VSN)
USB_VSYS: C10.1, C12.1, C13.1, C15.1, C25.1, R16.2, U2.8 (VSYS_1), U2.9 (VSYS_2), U2.22 (VSYS_3), U2.23 (VSYS_4), U2.24 (VSP)
UV_PWM: Q3.1 (G), R4.2, U3.1 (PD3)
VCC: C17.1, C19.1, C20.1, C21.1, C22.1, C33.1, C39.2, F1.1, L1.1, L2.2, M1.1 (+), Q5.2 (E), Q9.2 (S), Q10.2 (S), R1.1, R7.1, R17.2, R20.2, R25.2, R26.2, R28.2, R29.2, R30.2, R32.2, R33.2, U2.28 (BAT), U3.4 (VCC), U3.6 (VCC), U4.1 (VCCA), U5.1 (VCCA), U6.1 (VCCA), U6.5 (DIR)
VIBRO: Q13.1 (G), R35.2, U3.10 (PD6)
VREG: C32.1, R2.1, R3.1, R19.1, U1.2 (VREF1), U2.27 (VREG)
WAKEUP_BUTTON: C38.2, Q9.1 (G), Q11.1 (G), R30.1, SW2.1, U3.11 (PD7)

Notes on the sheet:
FIXME LIST on v2.0 KNOWN ERRORS: 1. required capacitor 22pF@500V on Y1 Fixes: 1. integrate UV stabilizator 2. replace L1 to AMPLF1040 3. rewrite amplifier-detector to work on positive impulse 4. remove unused JP2 5. add soldered jumper on UV_PWM line 6. add UV discharge button 7. replace GND testpo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
NOTE**** Test required
NOTE [****] Adjust this value to setup hold-to-reset time 400K + 100uF -> ~20 sec delay
T0 - clock [no pin output, ISR only] T1 - volume, vibro & LED flashlight. * OC1A -> volume generation with variable freq * OC1B -> flashlight brightness [used different duty of same timer] T2 - UV_PWM (hardware PWM on OC2B with fixed duty) Await impulses via ISR on INT0
NOTE*** Nmax for SBT11A == 2.5*10^4 imp/sec == 25Khz LF filter: 10K + 330pF ~ 48Khz Freq of UV source ~ 100hz
NOTE ** I have to find nominal of this R to reduce signal time MAX Timp = 1 / (2.5 * 10^4) = 40 mkS Expected Timp ~ 10-20mkS
T1: N in [1-2] : ~18 turns (change it to adjust output voltage) N out [3-4] : 1000 turns Ferite core : М2000НМ, Ш4х4, clearance - manual ~1-2mm, adjust it. Coil frame : Ш4х4 2 x https://www.chipdip.ru/product/m2000nm-sh4x4-1-sht 1 x https://www.chipdip.ru/product/katushka-karkas-pod-sh-4x4
NOTE* These capacitors used to adjust output voltage NOTE** This resistor can be used to adjust output voltage Use 10...100 ohm to reduce or increase it
WARNING! Check your LEDs! They must work on 3.5 ... 4.2V with correct current. Setup additional R to each LD in other case
You can use this R to reduce max volume. Use 0 ohm for max volume Be carefull with max-current of your speaker
NOTE [VSET?] One datasheet says 'Not installed for VCC=4.2V' But in another version of datasheet I saw something like 510K
USB_VSYS & USV_VMID lines: max ~ 25V
